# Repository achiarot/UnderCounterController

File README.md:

# UnderCounterController
This is an AVR(ATTINY 13A) CPP program and PCB for controlling undercounter LED strips.  They can be ganged together to control multiple strips and synchronize them.  The hardware will include a PIR (infrared motion) sensor which can be used to activate the LED strips.

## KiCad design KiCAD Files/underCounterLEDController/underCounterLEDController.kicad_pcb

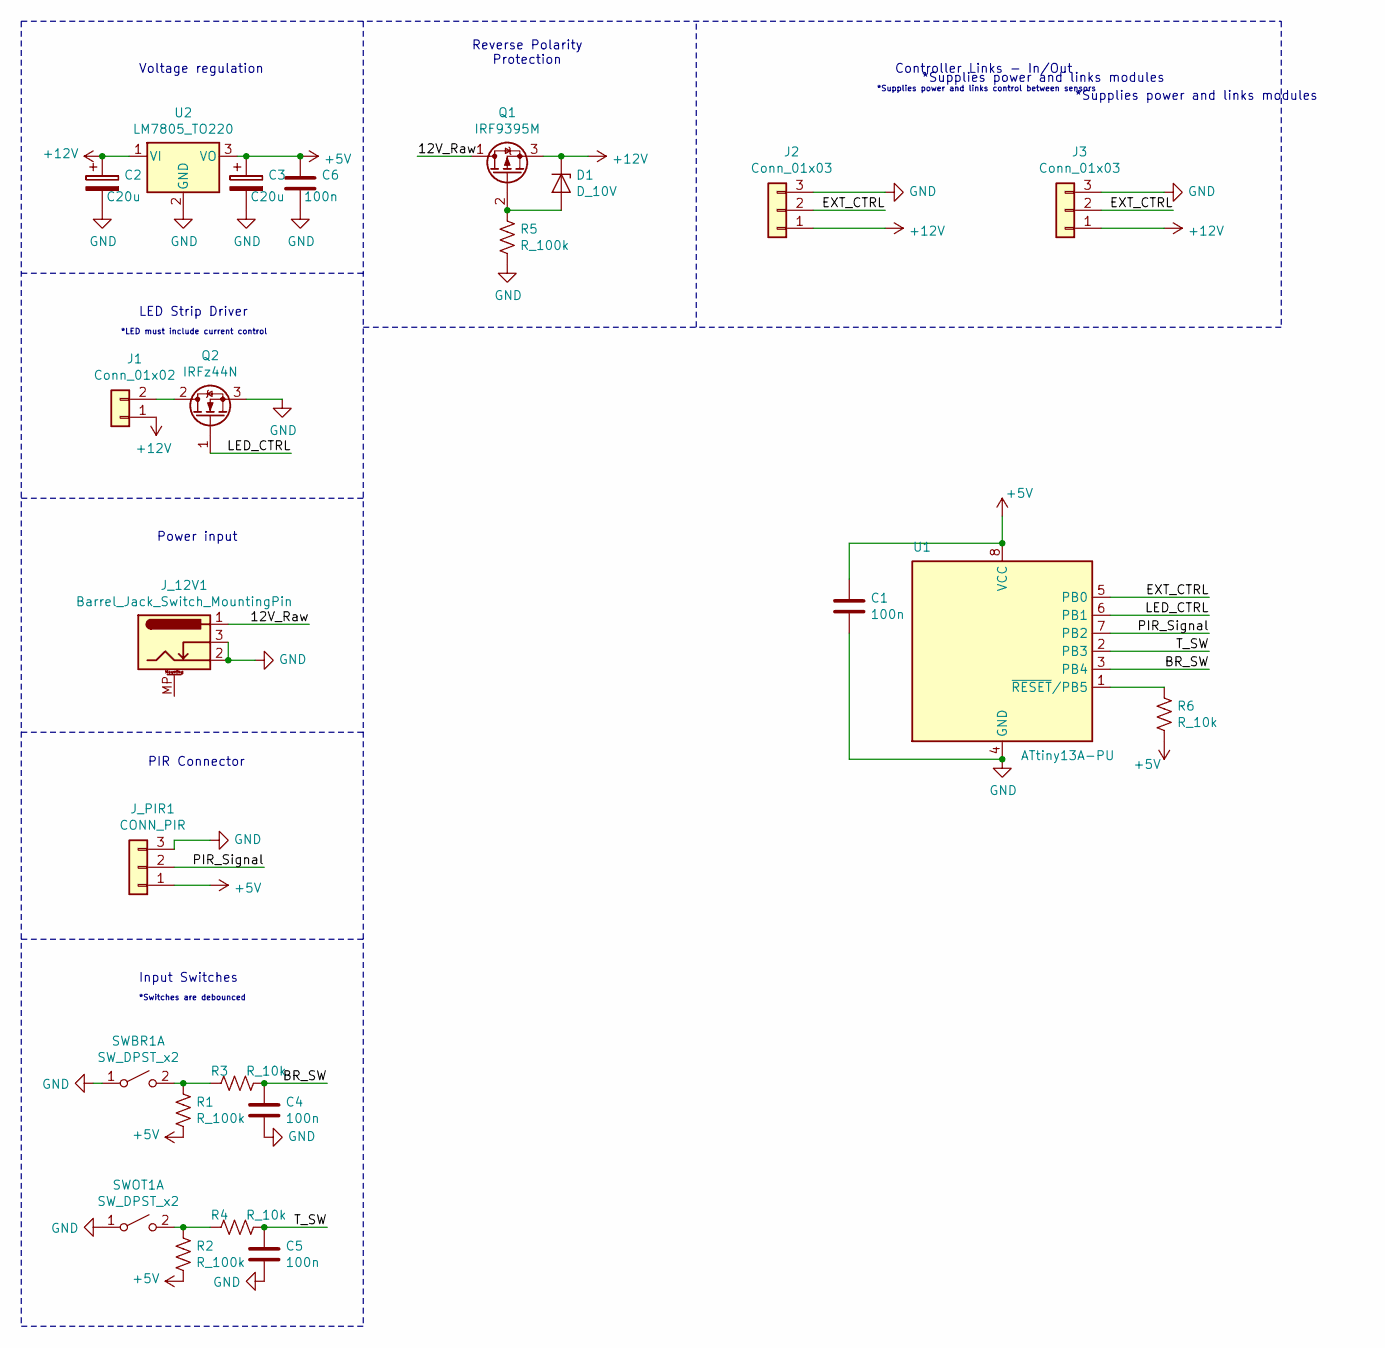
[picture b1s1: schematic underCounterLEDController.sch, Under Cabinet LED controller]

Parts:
C1, C4, C5, C6: 100n; C_Disc_D3.0mm_W1.6mm_P2.50mm
C2, C3: C20u; CP_Radial_D5.0mm_P2.00mm
D1: D_10V; D_DO-35_SOD27_P7.62mm_Horizontal
J1: Conn_01x02; PinSocket_1x02_P2.54mm_Horizontal
J2, J3: Conn_01x03; PinSocket_1x03_P2.54mm_Horizontal
J_12V1: Barrel_Jack_Switch_MountingPin; BarrelJack_Horizontal
J_PIR1: CONN_PIR; JST_XH_S03B-XH-A_1x03_P2.50mm_Horizontal
Q1: IRF9395M; TO-220-3_Horizontal_TabDown
Q2: IRFz44N; TO-220-3_Horizontal_TabDown
R1, R2, R5: R_100k; R_Axial_DIN0207_L6.3mm_D2.5mm_P10.16mm_Horizontal
R3, R4, R6: R_10k; R_Axial_DIN0207_L6.3mm_D2.5mm_P10.16mm_Horizontal
SWBR1: SW_DPST_x2; SW_PUSH_6mm_H5mm
SWOT1: SW_DPST_x2; SW_PUSH_6mm_H5mm
U1: ATtiny13A-PU; DIP-8_W7.62mm
U2: LM7805_TO220; TO-220-3_Horizontal_TabDown

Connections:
+5V: C1.1, C3.1, C6.1, J_PIR1.1, R1.2, R2.2, R6.2, U1.8 (VCC), U2.3 (VO)
+12V: C2.1, D1.1 (K), J1.1, J2.1, J3.1, Q1.3 (S), U2.1 (VI)
/12V_Raw: J_12V1.1, Q1.1 (D)
/BR_SW: C4.1, R3.2, U1.3 (PB4)
/EXT_CTRL: J2.2, J3.2, U1.5 (PB0)
/LED_CTRL: Q2.1 (G), U1.6 (PB1)
/PIR_Signal: J_PIR1.2, U1.7 (PB2)
/T_SW: C5.1, R4.2, U1.2 (PB3)
GND: C1.2, C2.2, C3.2, C4.2, C5.2, C6.2, J2.3, J3.3, J_12V1.2, J_12V1.3, J_PIR1.3, Q2.3 (S), R5.2, SWBR1.1 (A), SWOT1.1 (A), U1.4 (GND), U2.2 (GND)
unnamed: D1.2 (A), Q1.2 (G), R5.1
unnamed: J1.2, Q2.2 (D)
unnamed: R1.1, R3.1, SWBR1.2 (B)
unnamed: R2.1, R4.1, SWOT1.2 (B)
unnamed: R6.1, U1.1 (~RESET~/PB5)

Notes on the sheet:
Voltage regulation
LED Strip Driver
*LED must include current control
Power input
PIR Connector
Input Switches
*Switches are debounced
Reverse Polarity Protection
Controller Links - In/Out
*Supplies power and links modules
*Supplies power and links control between sensors

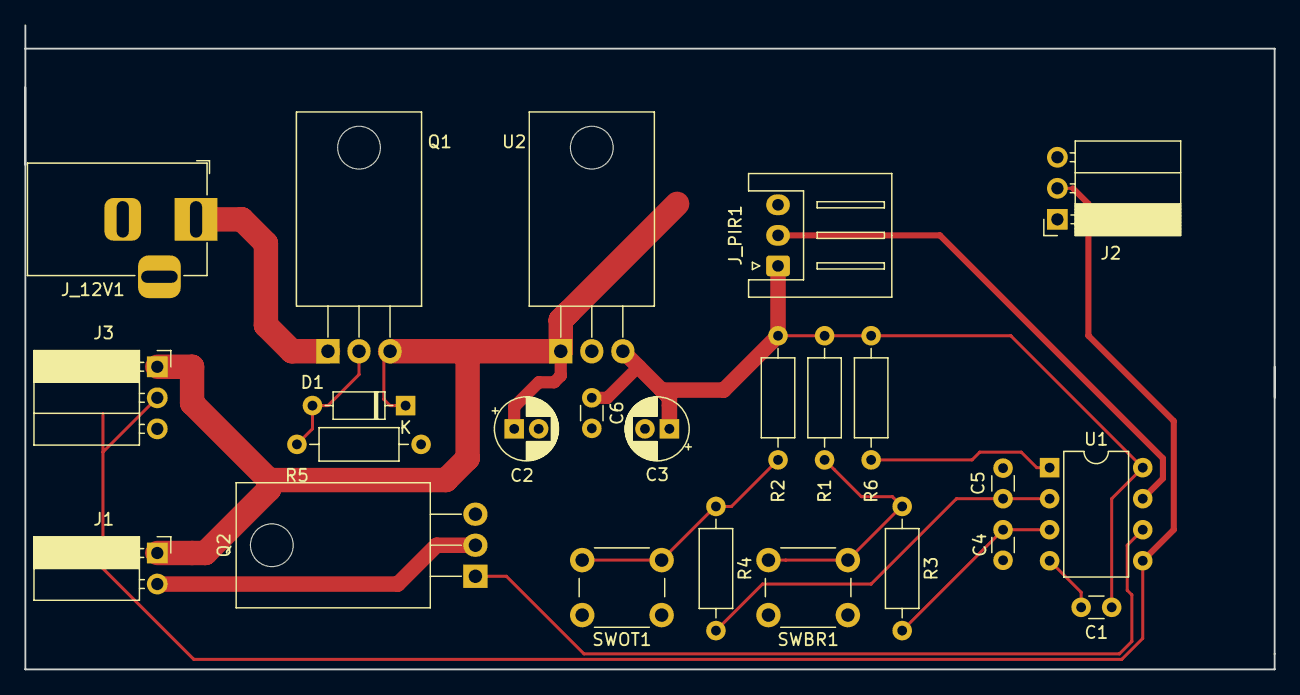
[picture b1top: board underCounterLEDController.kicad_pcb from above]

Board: 2 copper layers, 102.2 x 52.7 mm, 24 parts (0 on the bottom side), 14 nets.

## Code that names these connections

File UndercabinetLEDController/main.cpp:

/*
 * UndercabinetLEDController.cpp
 *
 * Created: 2019-10-12 2:45:41 PM
 * Author : antho
 */ 

#include <avr/io.h>
#include <avr/interrupt.h>
#include <avr/eeprom.h>

/* Configuration settings
	The following will include tuning parameters for LED max and min brightness for your  specific setup.
	PB3 - Input pin for on-time configuration
	PB4 - Input pin for Brightness control
	PB2 - Input pin for PIR sensor
	PB1 - PWM output for the LED driver
*/
#define TIMESW			PINB3
#define BRSW			PINB4
#define PIR				PINB2
#define LED				PINB1
#define LEDBR			OCR0B

#define MAXPWM			255
#define MINPWM			0
#define BR_STEP			25												//Brightness decrease per button press (must be positive)
#define P_FADE			3												//Seconds to fade LED on and off
#define MAXTIME_SEC		600												//Maximum amount of time on in seconds
#define MINTIME_SEC		10												//Minimum amount of time on in seconds
#define ONTIME_STEP_SEC	30												//Time on increase per button press (must be positive)
/* End of Configuration */

#define F_CPU			1200000LL
#define PRESCALER		1
#define F_PWM			((F_CPU/256)/PRESCALER)		
#define ONTIME_TICK_SEC	10												//Resolution of the onTime counter
#define P_OVFL			(ONTIME_TICK_SEC*F_PWM)							//Length of each ticks on the time counter
#define	COUNTDIVFADE	((P_FADE*F_PWM)/(MAXPWM))						//Calculated divisor to meet the fade period
#define COUNTBLINK		(F_PWM/5)										//Half a second blink
#define MAXTIME			(MAXTIME_SEC/ONTIME_TICK_SEC)
#define MINTIME			(MINTIME_SEC/ONTIME_TICK_SEC)
#define ONTIME_STEP		(uint8_t)(ONTIME_STEP_SEC/ONTIME_TICK_SEC)		//number of onTime ticks to last for
#define BR_ADDR			(uint8_t*)0x01									//address to store the current brightness in EEPROM for non volatile storage
#define OT_ADDR			(uint8_t*)0x02									//EEPROM address for onTime

/* Globally shared variable
	This includes variables shared or used by ISR's
*/
//
uint8_t PIRFlag;
volatile uint8_t BRFlag;
volatile uint8_t OTFlag;
volatile uint8_t ALWAYSONFlag;
									
volatile uint8_t lastSwitchState;

volatile uint8_t brightness;
volatile uint8_t onTime;										//LED on-time in 10 second increments

volatile uint16_t counterOverflow;								//Used for keeping track of on-time since we only have one timer
volatile uint8_t onCount;										//used for counting the 10 second intervals

int startTimer(){
	counterOverflow=0;											//Zero out the counters used to keep on time
	onCount=0;

	return 1;
}


int checkPIR(){
	if((PINB & (1<<PIR)) && !PIRFlag){
		PIRFlag = 1;
		startTimer();
		while(counterOverflow/COUNTDIVFADE < brightness){
			LEDBR = (255 - counterOverflow/COUNTDIVFADE);
		}
	}
	if(PINB & (1<<PIR)){
		startTimer();
	}
	if(PIRFlag){
		LEDBR = 255 - brightness;
	}
	if(PIRFlag && (onCount >= onTime) && !(onTime==MAXTIME)){
		PIRFlag = 0;
		startTimer();
		while(counterOverflow/COUNTDIVFADE < brightness){
			LEDBR = (255 - brightness + counterOverflow/COUNTDIVFADE);
		}
		LEDBR = 255;
	}
	if(ALWAYSONFlag){
		for(uint8_t i=0; i<2; i++){
			startTimer();
			LEDBR = 255;
			while(counterOverflow<COUNTBLINK ){}
			startTimer();
			LEDBR = 255-brightness;
			while(counterOverflow<COUNTBLINK ){}
		}
		ALWAYSONFlag=0;
	}
	return 1;
}

int main(void)
{
	//Setup inputs and outputs, as well as timers, PWM and interrupts
	DDRB = (DDRB | (1<<LED)) & ~((1<<PIR)|(1<<TIMESW)|(1<<BRSW));				//Set outputs and inputs
	PORTB = (PORTB | (1<<TIMESW) | (1<<BRSW)) & ~((1<<PIR)|(1<<LED));			//Set pullups for the buttons and explicitly not for the PIR
	
	TCCR0A |= (1<<COM0B1)|(1<<COM0B0)|(1<<WGM00)|(1<<WGM01);								//Set the timer for fast PWM
	TCCR0B |= (1<<CS00);												//Set the clock with no prescaler
    
	//Setup Pin change interrupt
	GIMSK |= (1<<PCIE);															//Enable in mask register
	PCMSK |= (1<<TIMESW)|(1<<BRSW);												//Mask all pins other than the two buttons and PIR
	
	/* DEBUGGING*/
	DDRB |= (1<<PINB0); //Make PB0 an output
	/* DEBUGGING End*/
	
	brightness = eeprom_read_byte(BR_ADDR);							//Read the stored value for brightness
	if(!((brightness>=MINPWM) && (brightness<=MAXPWM))){						//Sanity check the value, if not in the acceptable bounds, set to maximum value
		brightness = MAXPWM;
	}
	onTime = eeprom_read_byte(OT_ADDR);	
	if(!((onTime>=MINTIME) && (onTime<=MAXTIME))){								//Sanity check the value, if not in the acceptable bounds, set to minimum value
		onTime = MINTIME;
	}		
	counterOverflow=0;															//Zero out the counters used to keep on time
	onCount=0;
	PIRFlag=0;
	BRFlag=0;
	OTFlag=0;
	ALWAYSONFlag=0;
	lastSwitchState=0;

	LEDBR = 255;	
	TIMSK0 |= (1<<TOIE0);															//Default LED on-time is 30 seconds
	
	//Start interrupts
	sei();
	
    while (1)
    {
		checkPIR();
		if(BRFlag){
			eeprom_write_byte(BR_ADDR, brightness);
			BRFlag = 0;
		}
		if(OTFlag){
			eeprom_write_byte(OT_ADDR, onTime);
			OTFlag = 0;
		}
    }
}

ISR(TIM0_OVF_vect){
	
	if(counterOverflow>=P_OVFL){
		counterOverflow = 0;
		
		if(onCount>=onTime){
			onCount=onTime;											//Hold at the max time so you can deal with it in the main function
		}
		else{
			onCount++;
		}
	}
	
	else{
		counterOverflow++;
	}
}

ISR(PCINT0_vect, ISR_NOBLOCK){
	
	uint8_t state = PINB;						//Read the state of the port immediately
	
	/*DEBUGGING*/
	PORTB |= (1<<PINB0);
	/*DEBUGGING END*/
	
	//Split into the two possible interrupt sources and handle each
	if((~state & (1<<TIMESW)) && (lastSwitchState & (1<<TIMESW))){
		//The time switch has been pressed
		if(onTime == MAXTIME){
			onTime = MINTIME;
		}
		else if(onTime >= ((MAXTIME-ONTIME_STEP))){
			onTime = MAXTIME;
			ALWAYSONFlag = 1;
		}
		else{
			onTime += ONTIME_STEP;
		}
		OTFlag=1;
	}
	
	if((~state & (1<<BRSW)) && (lastSwitchState & (1<<BRSW))){
		//The brightness has been adjusted
		if(brightness == 0){
			brightness = MAXPWM;
		}
		else if(brightness == MINPWM){
			brightness = 0;
		}
		else if(brightness<=(BR_STEP+MINPWM)){
			brightness = MINPWM;
		}
		else{ 
			brightness -= BR_STEP;
		}
		BRFlag = 1;
	}
	lastSwitchState=state;
	/*DEBUGGING*/
	PORTB &= ~(1<<PINB0);
	/*DEBUGGING END*/
}

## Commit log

2019-10-24 Added ATMEL Studio Project
2019-10-24 Added KiCAD PCB files
2019-10-24 Updated file structure
